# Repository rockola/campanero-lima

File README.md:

# campanero-lima
Green Ringer-like octave up

See https://www.diystompboxes.com/smfforum/index.php?topic=125681.0 for more info.

* v0.1: initial version

# LICENSE

MIT

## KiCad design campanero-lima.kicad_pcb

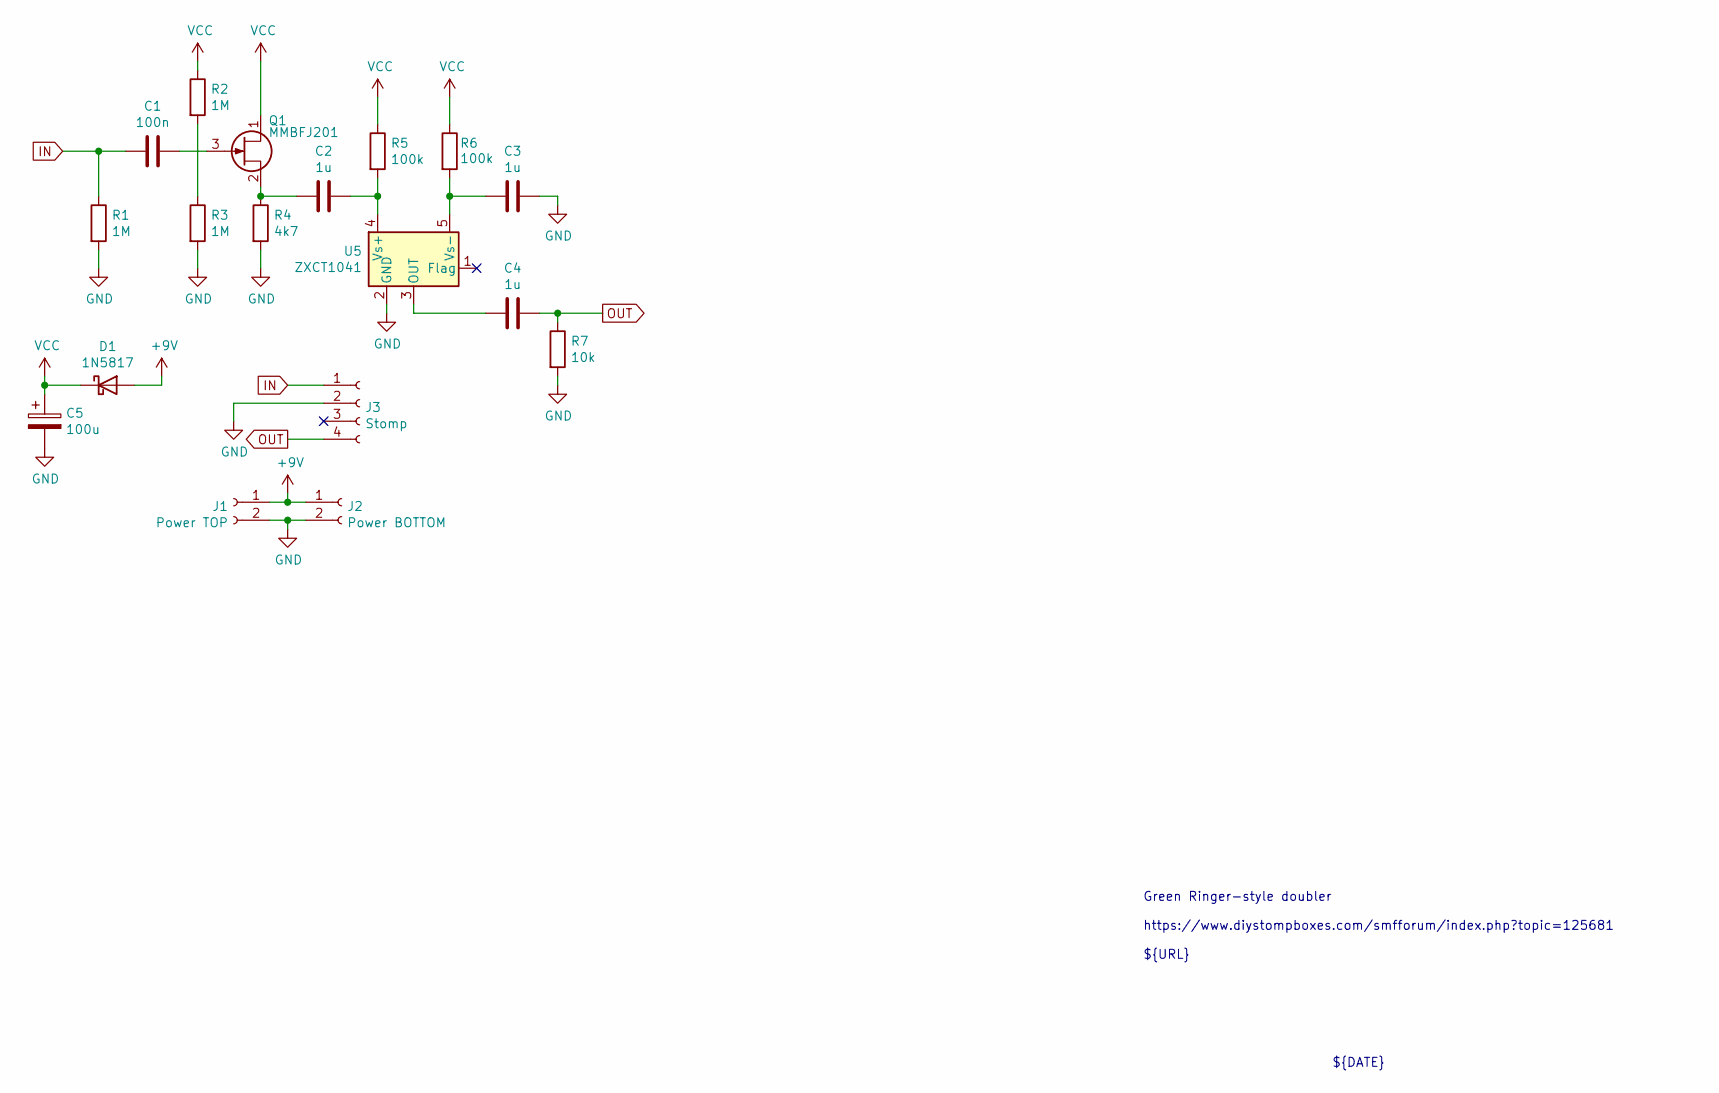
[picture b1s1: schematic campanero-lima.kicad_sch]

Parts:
C1: 100n; C_Box_7.2_2.5
C2, C3, C4: 1u; C_Box_7.2_5.0
C5: 100u; CP_D6.3_P2.50
D1: 1N5817; D_DO-41_SOD81_P10.16mm_Horizontal
J1: Power TOP; Power_Header_2pin_TOP
J2: Power BOTTOM; Power_Header_2pin
J3: Stomp; Stomp_4pin
Q1: MMBFJ201; SOT-23
R1, R2, R3: 1M; R_DIN0207
R4: 4k7; R_DIN0207
R5, R6: 100k; R_DIN0207
R7: 10k; R_DIN0207
U5: ZXCT1041; SOT-23-5

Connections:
+9V: D1.2 (A), J1.1, J2.1
GND: C3.2, C5.2, J1.2, J2.2, J3.2, R1.2, R3.2, R4.2, R7.2, U5.2 (GND)
IN: C1.1, J3.1, R1.1
unnamed: C1.2, Q1.3 (G)
unnamed: C4.1, U5.3 (OUT)
unnamed: R2.2, R3.1
unnamed: C2.1, Q1.2 (S), R4.1
unnamed: C2.2, R5.2, U5.4 (Vs+)
unnamed: C3.1, R6.2, U5.5 (Vs-)
OUT: C4.2, J3.4, R7.1
VCC: C5.1, D1.1 (K), Q1.1 (D), R2.1, R5.1, R6.1

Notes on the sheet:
${TITLE}
${REVISION}
Green Ringer-style doubler https://www.diystompboxes.com/smfforum/index.php?topic=125681 ${URL}
${DATE}

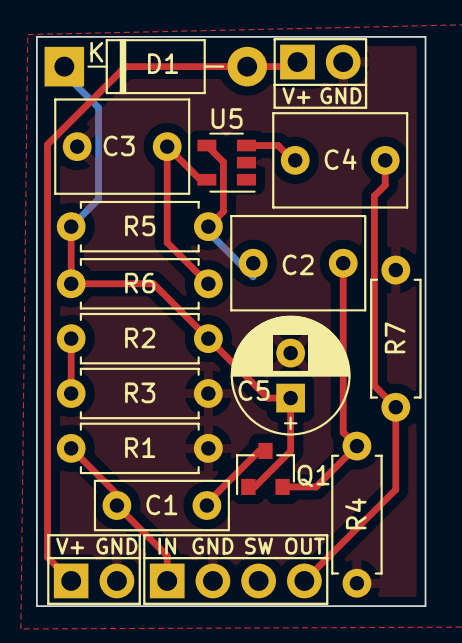
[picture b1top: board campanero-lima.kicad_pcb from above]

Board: 2 copper layers, 21.6 x 31.6 mm, 18 parts (0 on the bottom side), 11 nets.

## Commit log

2020-10-27 initial version
2020-10-27 main branch is now main
2022-01-11 updated to KiCad 6.0
